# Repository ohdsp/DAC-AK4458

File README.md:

# [Open Hardware DSP Platform](http://www.ohdsp.org)
## DAC-AK4458
### Revision 1.0
### 8 Differential DAC Output Board

---
# README
### Disclaimer
Copyright Paul Janicki 2019

Licensed under the TAPR Open Hardware License (www.tapr.org/OHL)

This documentation is distributed WITHOUT ANY EXPRESS OR IMPLIED WARRANTY, INCLUDING OF MERCHANTABILITY, SATISFACTORY QUALITY AND FITNESS FOR A PARTICULAR PURPOSE.

### What is this repository?

**Quick summary**

This is Open Hardware DSP Platform DAC-AK4458 Revision 1.0. 

This is an 8 differential outputb DAC board based on the AK4458.

This repository contains the KiCad design files, manufacturing Gerber/drill files, PDF/drawing files, and relevant documenation for this board.

### What is the project folder structure?
Most folder names are self explanatory. Starting from the top level: \
*DAC-AK4458*
+ *Bill of Materials*  - This contains the bill of materials in CVS, LibreOffice Calc and XML formats
+ *Drawings* - This contains PDF and SVG Schematic and PCB files
+ *Gerbers* - This contains the PCB Gerbers and drill drawings for manufacture, there is also a zip file ready to send to most manufacturers
+ *JPEGs* - JPEGs of top and bottom views from 3D viewer
+ *KiCad* - This contains the original KiCad schematic and PCB design files
+ *Pick and Place* - This contains pick and place files for top and bottom sides
### How do I get set up?

**Summary of set up**

1. Set your self up a directory on a local disk, something simple will make life easier (eg C:\Electronics on Windows as used here), but anywhere will do just fine.
2. Download the Kicad-Libs from [https://github.com/ohdsp/KiCad-Libs](https://github.com/ohdsp/KiCad-Libs) and place in C:\Electronics\Kicad-Libs (or your chosen folder) 
3. Create a OHDSP subdirectory in C:\Electronics (so C:\Electronics\OHDSP)
3. Download this project to C:\Electronics\OHDSP\DAC-AK4458
4. Fire up Kicad
5. Open the main project file C:\Electronics\OHDSP\DAC-AK4458\KiCad\DAC-AK4458-1.0.pro
7. Do as you wish with the project, just keep it under the TAPR Open Hardware License.
Note: For library issues see below.

Make sure your git setup doesn't exclude files used in the project (like .LIB files) or things may go wrong down the line.

**KiCad Library Configuration**

Note that libraries are setup using relative paths, if you follow the above instructions things should work just fine. Below is the default library setup.

To setup eeschema component libraries:
From KiCad main window go to menu Tools -> Edit Schematic Symbols. In the new Window go to menu Preferences -> Manage Symbol Libraries.

On the new "Symbol Libraries" window select the "Project Specific Libraries" tab. The "Append Library" and "Remove Library" buttons can be used to add/remove enteries.
The standard setup is:

|   | Active | Nickname        | Library Path                                        | Plugin Type | Options | Description |
|---|--------|-----------------|-----------------------------------------------------|-------------|---------|-------------|
| 1 | Ticked | power           | ${KICAD_SYMBOL_DIR}/power.lib                       | Legacy      | (blank) | (blank)     |
| 2 | Ticked | MyKiCadLibs-Lib | ${KIPRJMOD}/../../../KiCad-Libs/MyKiCadLibs-Lib.lib | Legacy      | (blank) | (blank)     |

${KICAD_SYMBOL_DIR}  is set under the Enviromnet Variable Configuration. Close Symbol Libraries dialogue and go "Preferences" -> "Configure Paths..."

${KICAD_SYMBOL_DIR} is set to C:\Program Files\KiCad\share\kicad\library - this is the default for a KiCad install on the C drive

${KIPRJMOD} is automatically set to the location of the project (.pro file), in this example this would be C:\Electronics\OHDSP\uDSP\KiCad

To setup Pcbnew libraries:
From KiCad main window go to menu Tools -> Edit PCB Footprints. In the new Window go to menu Preferences -> Manage Symbol Libraries.

On the new "Symbol Libraries" window select the "Project Specific Libraries" tab. The "Append Library" and "Remove Library" buttons can be used to add/remove enteries.
The standard setup is:

|   | Active | Nickname               | Library Path                                                  | Plugin Type | Options | Description |
|---|--------|------------------------|---------------------------------------------------------------|-------------|---------|-------------|
| 1 | Ticked | MyKiCadLibs-Footprints | ${KIPRJMOD}/../../../KiCad-Libs/MyKiCadLibs-Footprints.pretty | KiCad       | (blank) | (blank)     |

${KIPRJMOD} is automatically set to the location of the project (.pro file), in this example this would be C:\Electronics\OHDSP\uDSP\KiCad

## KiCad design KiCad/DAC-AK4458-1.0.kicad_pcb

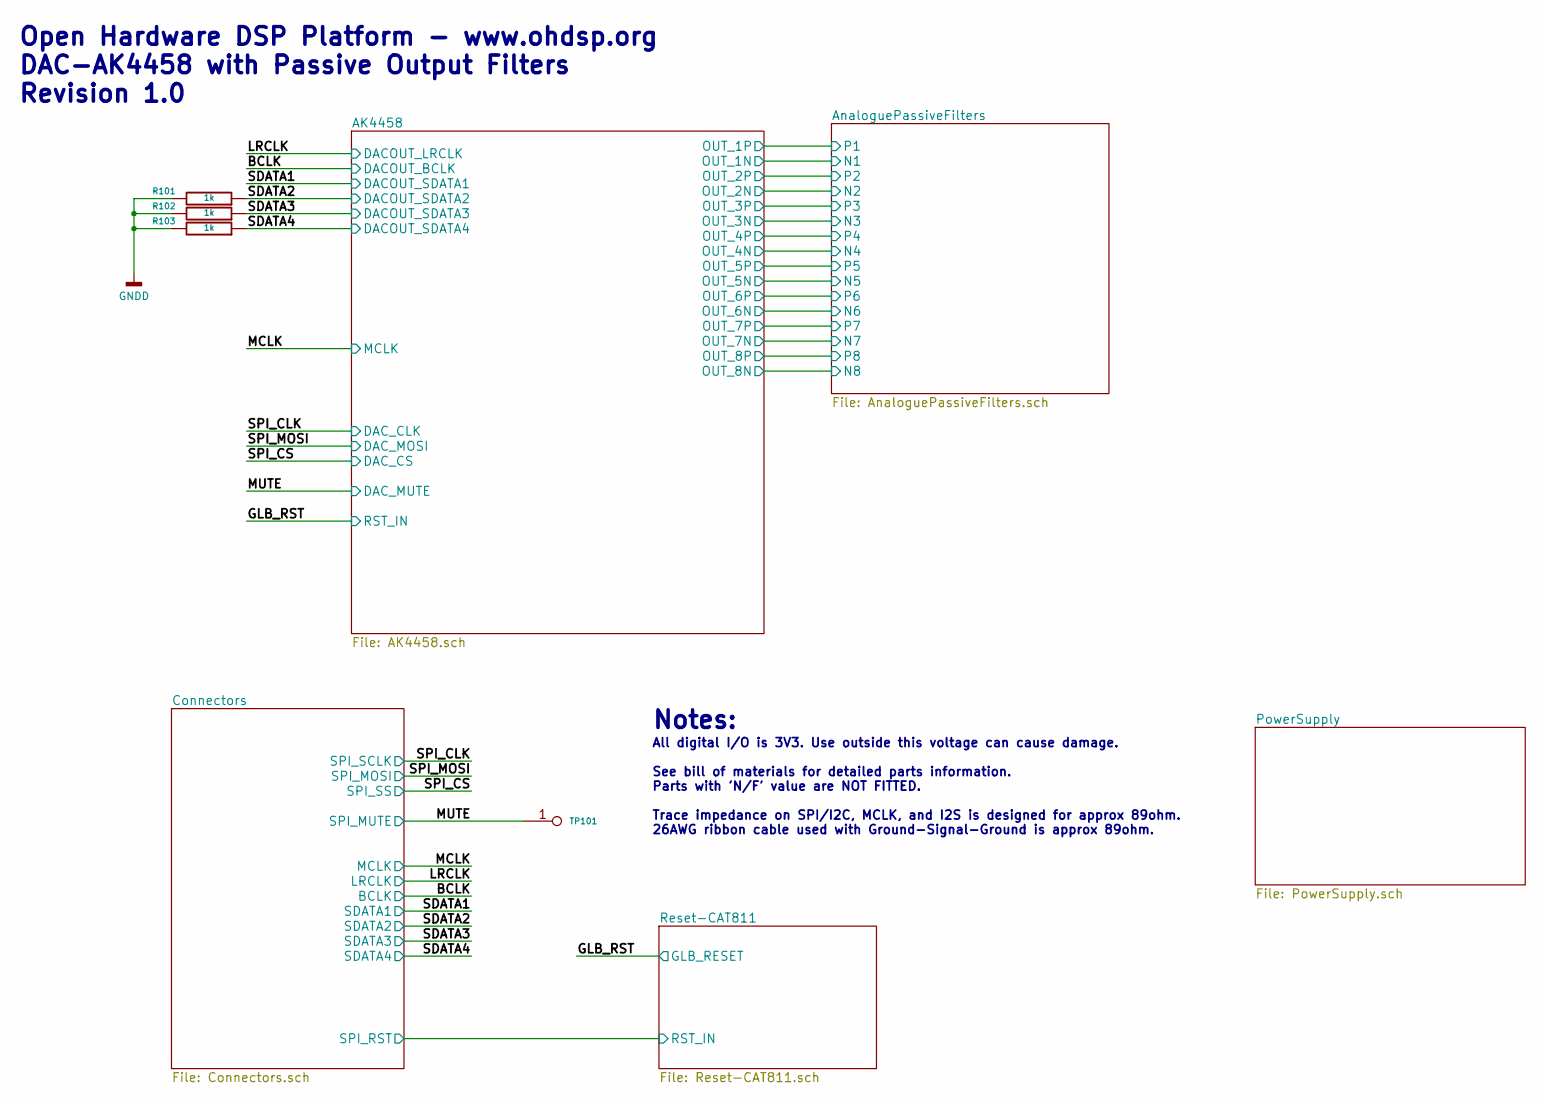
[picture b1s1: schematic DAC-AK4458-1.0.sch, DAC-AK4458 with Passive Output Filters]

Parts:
R101, R102, R103: 1k; SMD-0805; Tolerance 1%
TP101: Test point; TP-1mm

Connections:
/MUTE: TP101.1; also elsewhere on the board
/SDATA2: R101.1; also elsewhere on the board
/SDATA3: R102.1; also elsewhere on the board
/SDATA4: R103.1; also elsewhere on the board
GNDA: R101.2, R102.2, R103.2; also elsewhere on the board

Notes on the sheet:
Open Hardware DSP Platform - www.ohdsp.org DAC-AK4458 with Passive Output Filters Revision 1.0
All digital I/O is 3V3. Use outside this voltage can cause damage. See bill of materials for detailed parts information. Parts with 'N/F' value are NOT FITTED. Trace impedance on SPI/I2C, MCLK, and I2S is designed for approx 89ohm. 26AWG ribbon cable used with Ground-Signal-Ground is approx 89ohm.
Notes:

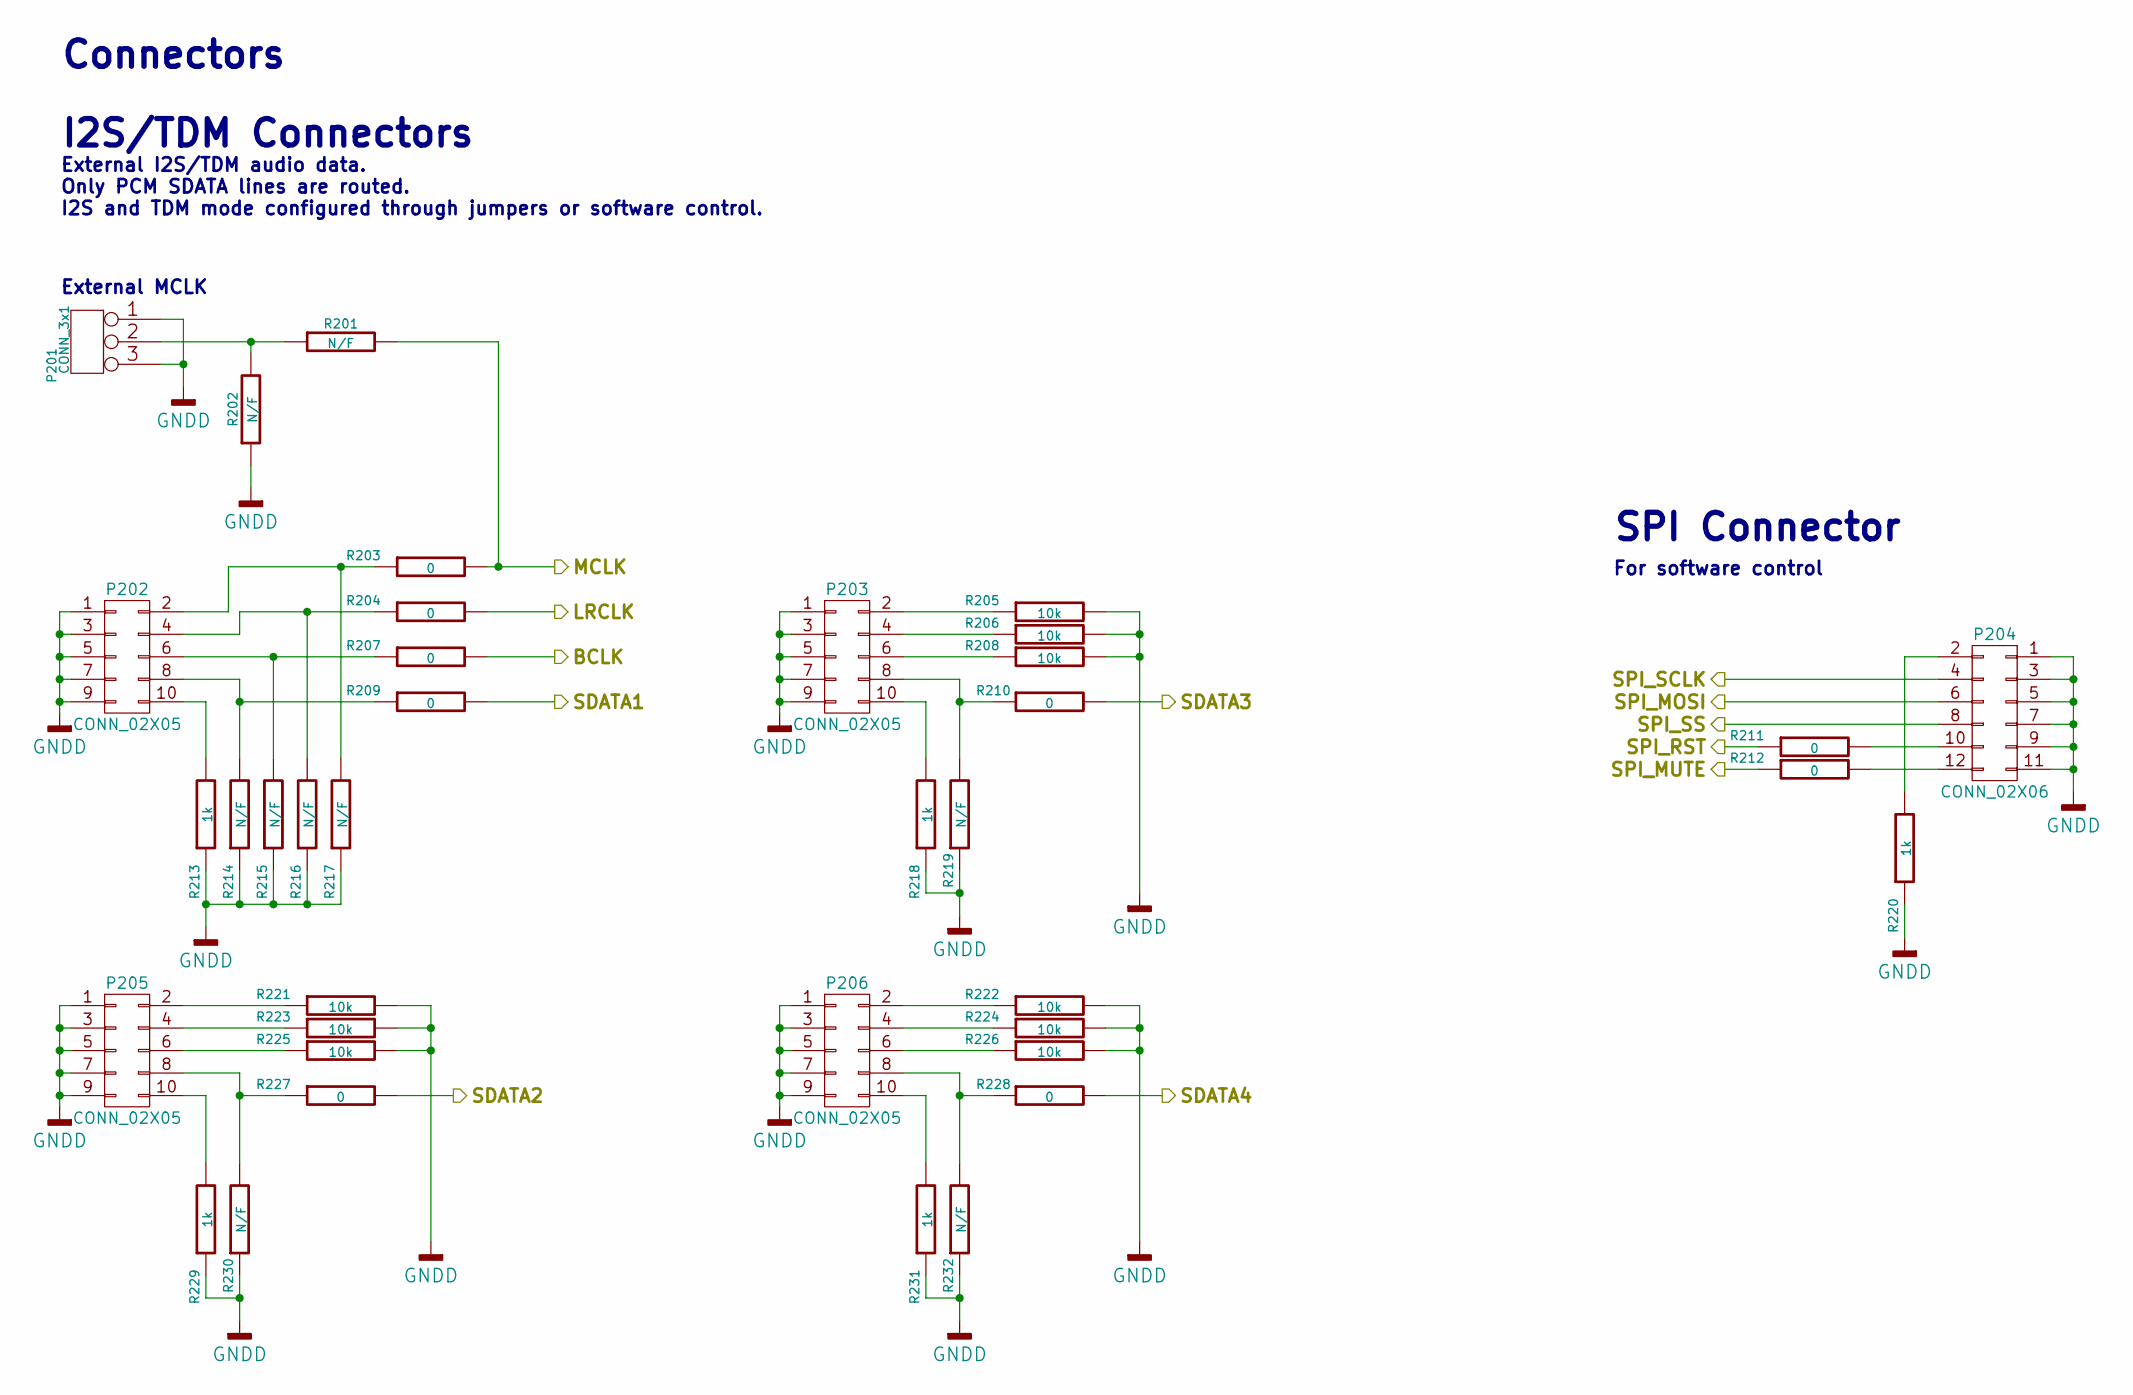
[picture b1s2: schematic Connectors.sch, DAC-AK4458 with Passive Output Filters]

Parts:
P201: CONN_3x1; CONN_SIL_3_1MM
P202, P203, P205, P206: CONN_02X05; CONN_DIL_2X5_BOX_1MM
P204: CONN_02X06; CONN_DIL_2X6_BOX_1MM
R201, R202, R214, R215, R216, R217, R219, R230, R232: N/F; SMD-0805; Tolerance 1%
R203, R204, R207, R209, R210, R211, R212, R227, R228: 0; SMD-0805; Tolerance 1%
R205, R206, R208, R221, R222, R223, R224, R225, R226: 10k; SMD-0805; Tolerance 1%
R213, R218, R220, R229, R231: 1k; SMD-0805; Tolerance 1%

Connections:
/BCLK: R207.2; also elsewhere on the board
/LRCLK: R204.2; also elsewhere on the board
/MCLK: R201.2, R203.2; also elsewhere on the board
/MUTE: R212.1; also elsewhere on the board
/Reset-CAT811/RST_IN: R211.1; also elsewhere on the board
/SDATA1: R209.2; also elsewhere on the board
/SDATA2: R227.2; also elsewhere on the board
/SDATA3: R210.2; also elsewhere on the board
/SDATA4: R228.2; also elsewhere on the board
/SPI_CLK: P204.4; also elsewhere on the board
/SPI_CS: P204.8; also elsewhere on the board
/SPI_MOSI: P204.6; also elsewhere on the board
GNDA: P201.1, P201.3, P202.1, P202.3, P202.5, P202.7, P202.9, P203.1, P203.3, P203.5, P203.7, P203.9, P204.1, P204.3, P204.5, P204.7, P204.9, P204.11, P205.1, P205.3, P205.5, P205.7, P205.9, P206.1, P206.3, P206.5, P206.7, P206.9, R202.1, R205.2, R206.2, R208.2, R213.1, R214.1, R215.1, R216.1, R217.1, R218.1, R219.1, R220.1, R221.2, R222.2, R223.2, R224.2, R225.2, R226.2, R229.1, R230.1, R231.1, R232.1; also elsewhere on the board
unnamed: P201.2, R201.1, R202.2
unnamed: P202.2, R203.1, R217.2
unnamed: P202.4, R204.1, R216.2
unnamed: P202.6, R207.1, R215.2
unnamed: P202.8, R209.1, R214.2
unnamed: P202.10, R213.2
unnamed: P203.2, R205.1
unnamed: P203.4, R206.1
unnamed: P203.6, R208.1
unnamed: P203.8, R210.1, R219.2
unnamed: P203.10, R218.2
unnamed: P204.2, R220.2
unnamed: P204.10, R211.2
unnamed: P204.12, R212.2
unnamed: P205.2, R221.1
unnamed: P205.4, R223.1
unnamed: P205.6, R225.1
unnamed: P205.8, R227.1, R230.2
unnamed: P205.10, R229.2
unnamed: P206.2, R222.1
unnamed: P206.4, R224.1
unnamed: P206.6, R226.1
unnamed: P206.8, R228.1, R232.2
unnamed: P206.10, R231.2

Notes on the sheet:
SPI Connector
I2S/TDM Connectors
External MCLK
External I2S/TDM audio data. Only PCM SDATA lines are routed. I2S and TDM mode configured through jumpers or software control.
For software control
Connectors

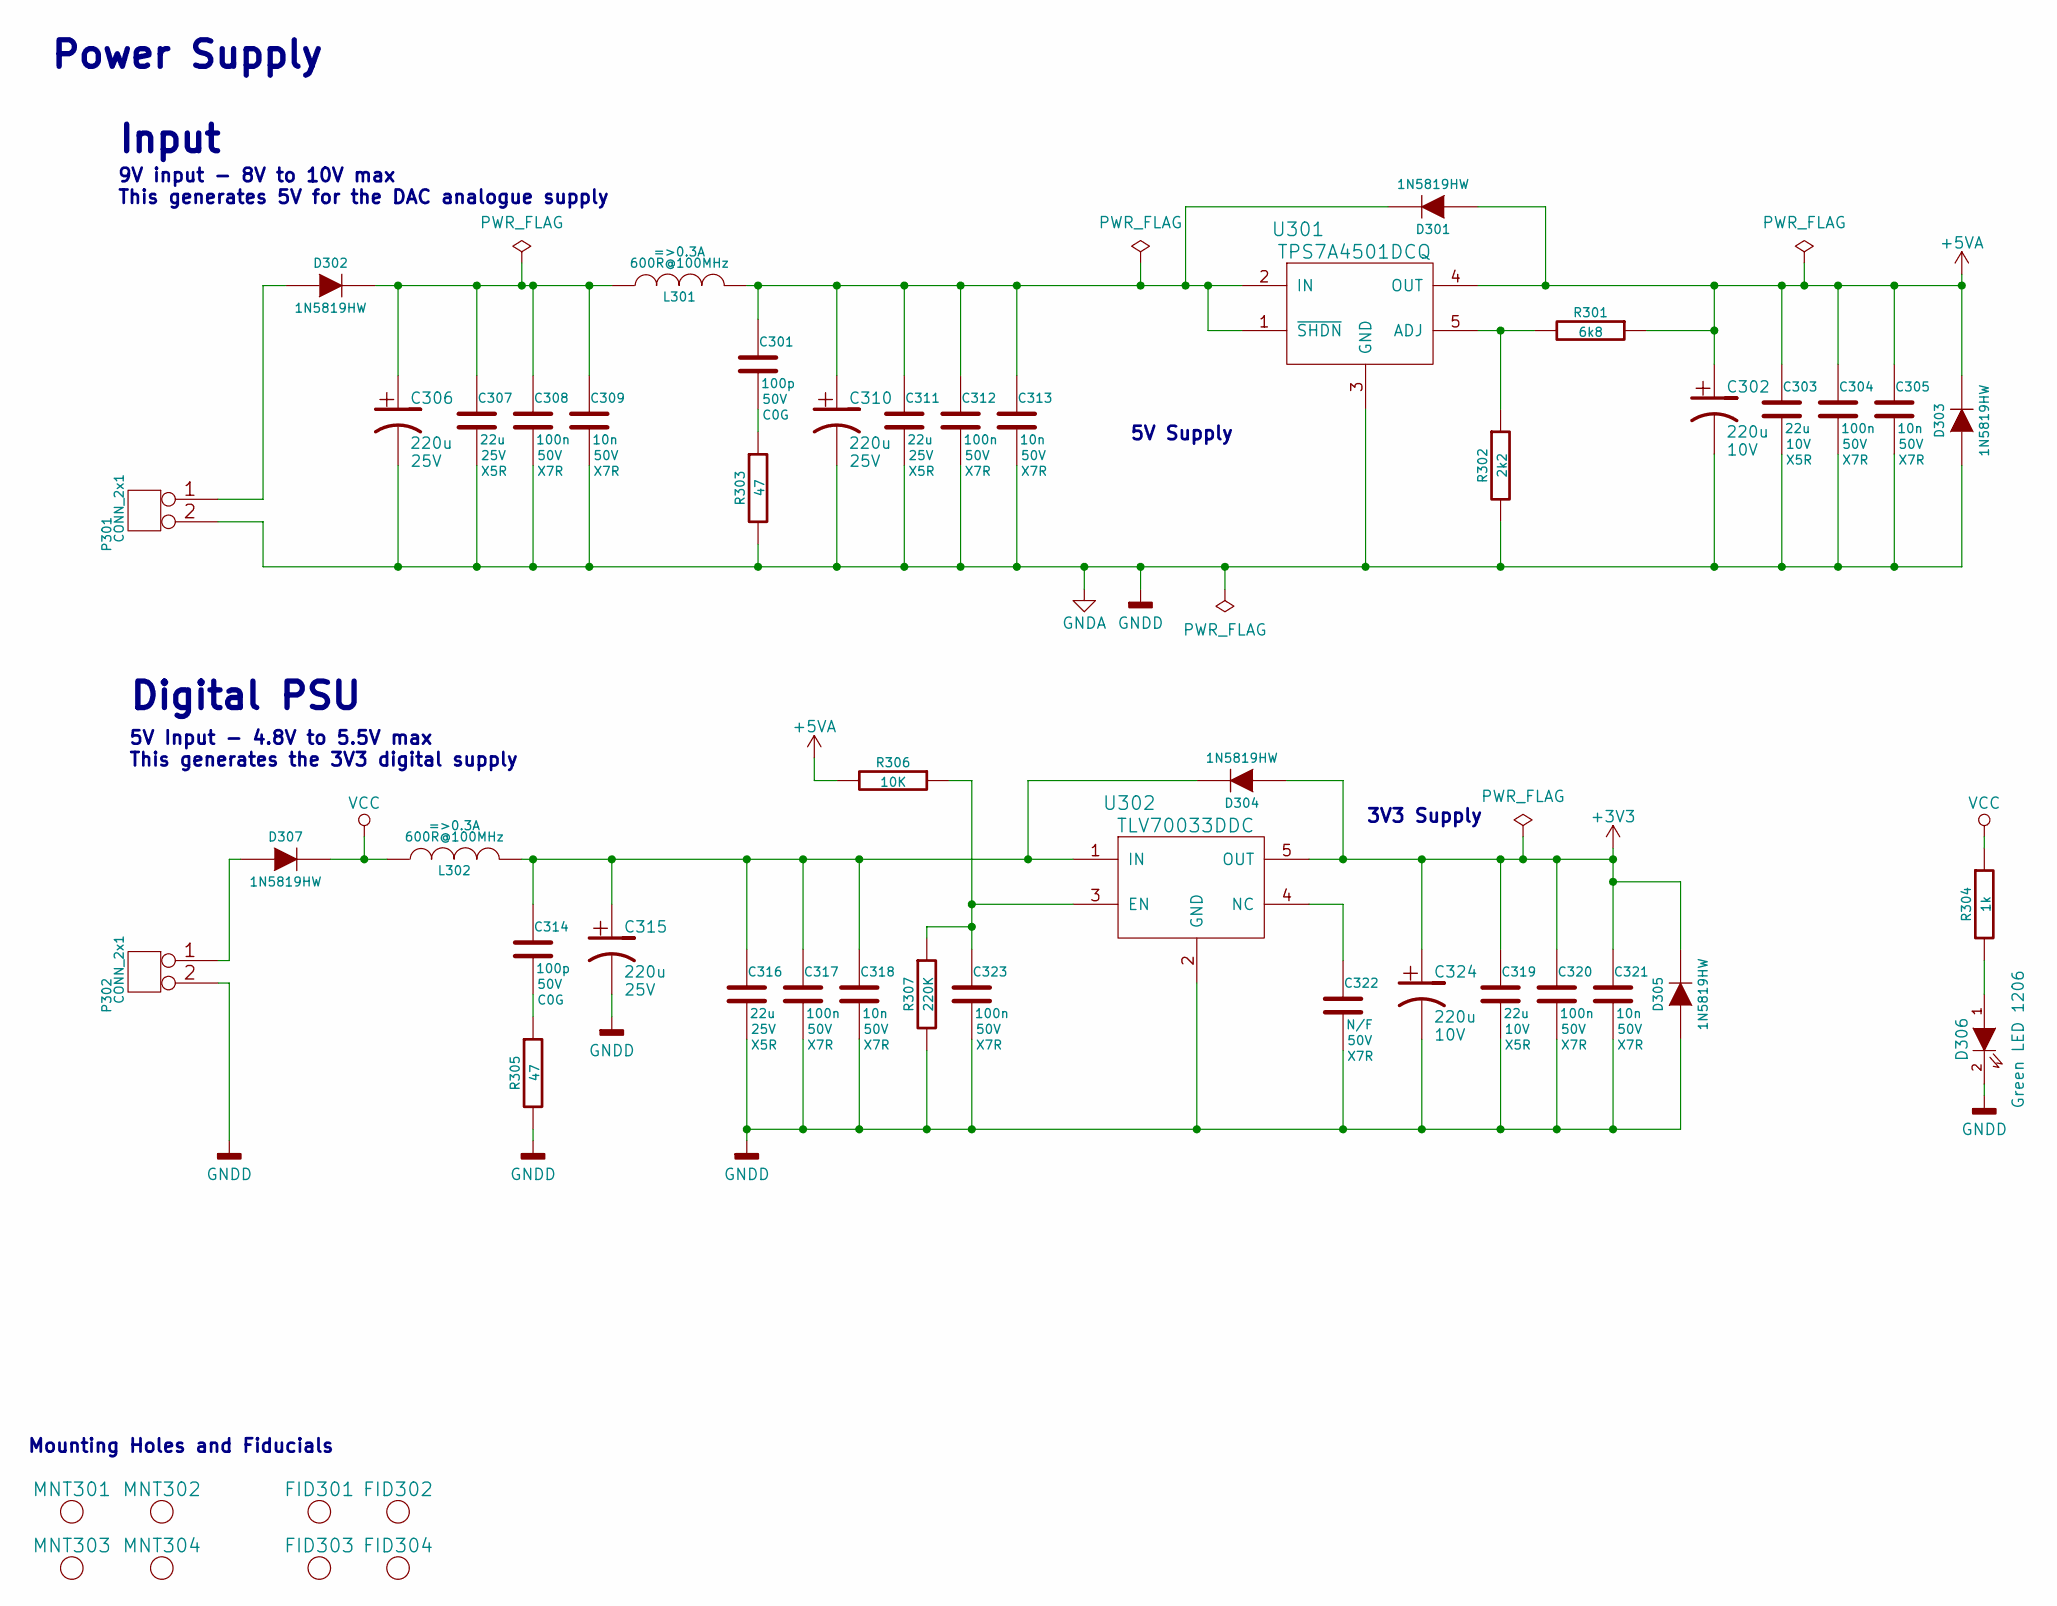
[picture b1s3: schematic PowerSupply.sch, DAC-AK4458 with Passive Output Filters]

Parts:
C301, C314: 100p; SMD-0805; Voltage 50V; Tolerance 5%
C302, C324: 220u; CAP-TH-D6.3mmP2.5mm; Voltage 10V
C303, C319: 22u; SMD-0805; Voltage 10V; Tolerance 20%
C304, C308, C312, C317, C320, C323: 100n; SMD-0805; Voltage 50V; Tolerance 10%
C305, C309, C313, C318, C321: 10n; SMD-0805; Voltage 50V; Tolerance 10%
C306, C310, C315: 220u; CAP-TH-D8mmP3.5mm; Voltage 25V
C307, C311, C316: 22u; SMD-0805; Voltage 25V; Tolerance 20%
C322: N/F; SMD-0805; Voltage 50V; Tolerance 10%
D301, D302, D303, D304, D305, D307: 1N5819HW; DIODE-SOD-123
D306: Green LED 1206; SMD-1206
FID301, FID302, FID303, FID304: MNT_HOLE; FID-1MM-3MM
L301, L302: 600R@100MHz; SMD-0805
MNT301, MNT302, MNT303, MNT304: MNT_HOLE; MNT_HOLE_3.2mm
P301, P302: CONN_2x1; CONN-2WAY-2.54mm-3.81mm-SPACING
R301: 6k8; SMD-0805; Tolerance 1%
R302: 2k2; SMD-0805; Tolerance 1%
R303, R305: 47; SMD-0805; Tolerance 1%
R304: 1k; SMD-0805; Tolerance 1%
R306: 10K; SMD-0805; Tolerance 1%
R307: 220K; SMD-0805; Tolerance 1%
U301: TPS7A4501DCQ; IC-SOT223-6
U302: TLV70033DDC; IC-SOT23-5

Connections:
+3V3: C319.1, C320.1, C321.1, C324.1, D304.1 (A), D305.2 (K), U302.5 (OUT); also elsewhere on the board
+5VA: C302.1, C303.1, C304.1, C305.1, D301.1 (A), D303.2 (K), R301.1, R306.2, U301.4 (OUT); also elsewhere on the board
GNDA: C302.2, C303.2, C304.2, C305.2, C306.2, C307.2, C308.2, C309.2, C310.2, C311.2, C312.2, C313.2, C315.2, C316.2, C317.2, C318.2, C319.2, C320.2, C321.2, C322.2, C323.2, C324.2, D303.1 (A), D305.1 (A), D306.2 (K), P301.2, P302.2, R302.2, R303.2, R305.2, R307.2, U301.3 (GND), U302.2 (GND); also elsewhere on the board
unnamed: C301.1, C310.1, C311.1, C312.1, C313.1, D301.2 (K), L301.2, U301.1 (~SHDN), U301.2 (IN)
unnamed: C301.2, R303.1
unnamed: C306.1, C307.1, C308.1, C309.1, D302.2 (K), L301.1
unnamed: C314.1, C315.1, C316.1, C317.1, C318.1, D304.2 (K), L302.2, U302.1 (IN)
unnamed: C314.2, R305.1
unnamed: C322.1, U302.4 (NC)
unnamed: C323.1, R306.1, R307.1, U302.3 (EN)
unnamed: D302.1 (A), P301.1
unnamed: D306.1 (A), R304.2
unnamed: D307.1 (A), P302.1
unnamed: R301.2, R302.1, U301.5 (ADJ)
VCC: D307.2 (K), L302.1, R304.1

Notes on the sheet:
Mounting Holes and Fiducials
Input
Digital PSU
9V input - 8V to 10V max This generates 5V for the DAC analogue supply
5V Input - 4.8V to 5.5V max This generates the 3V3 digital supply
5V Supply
3V3 Supply
Power Supply

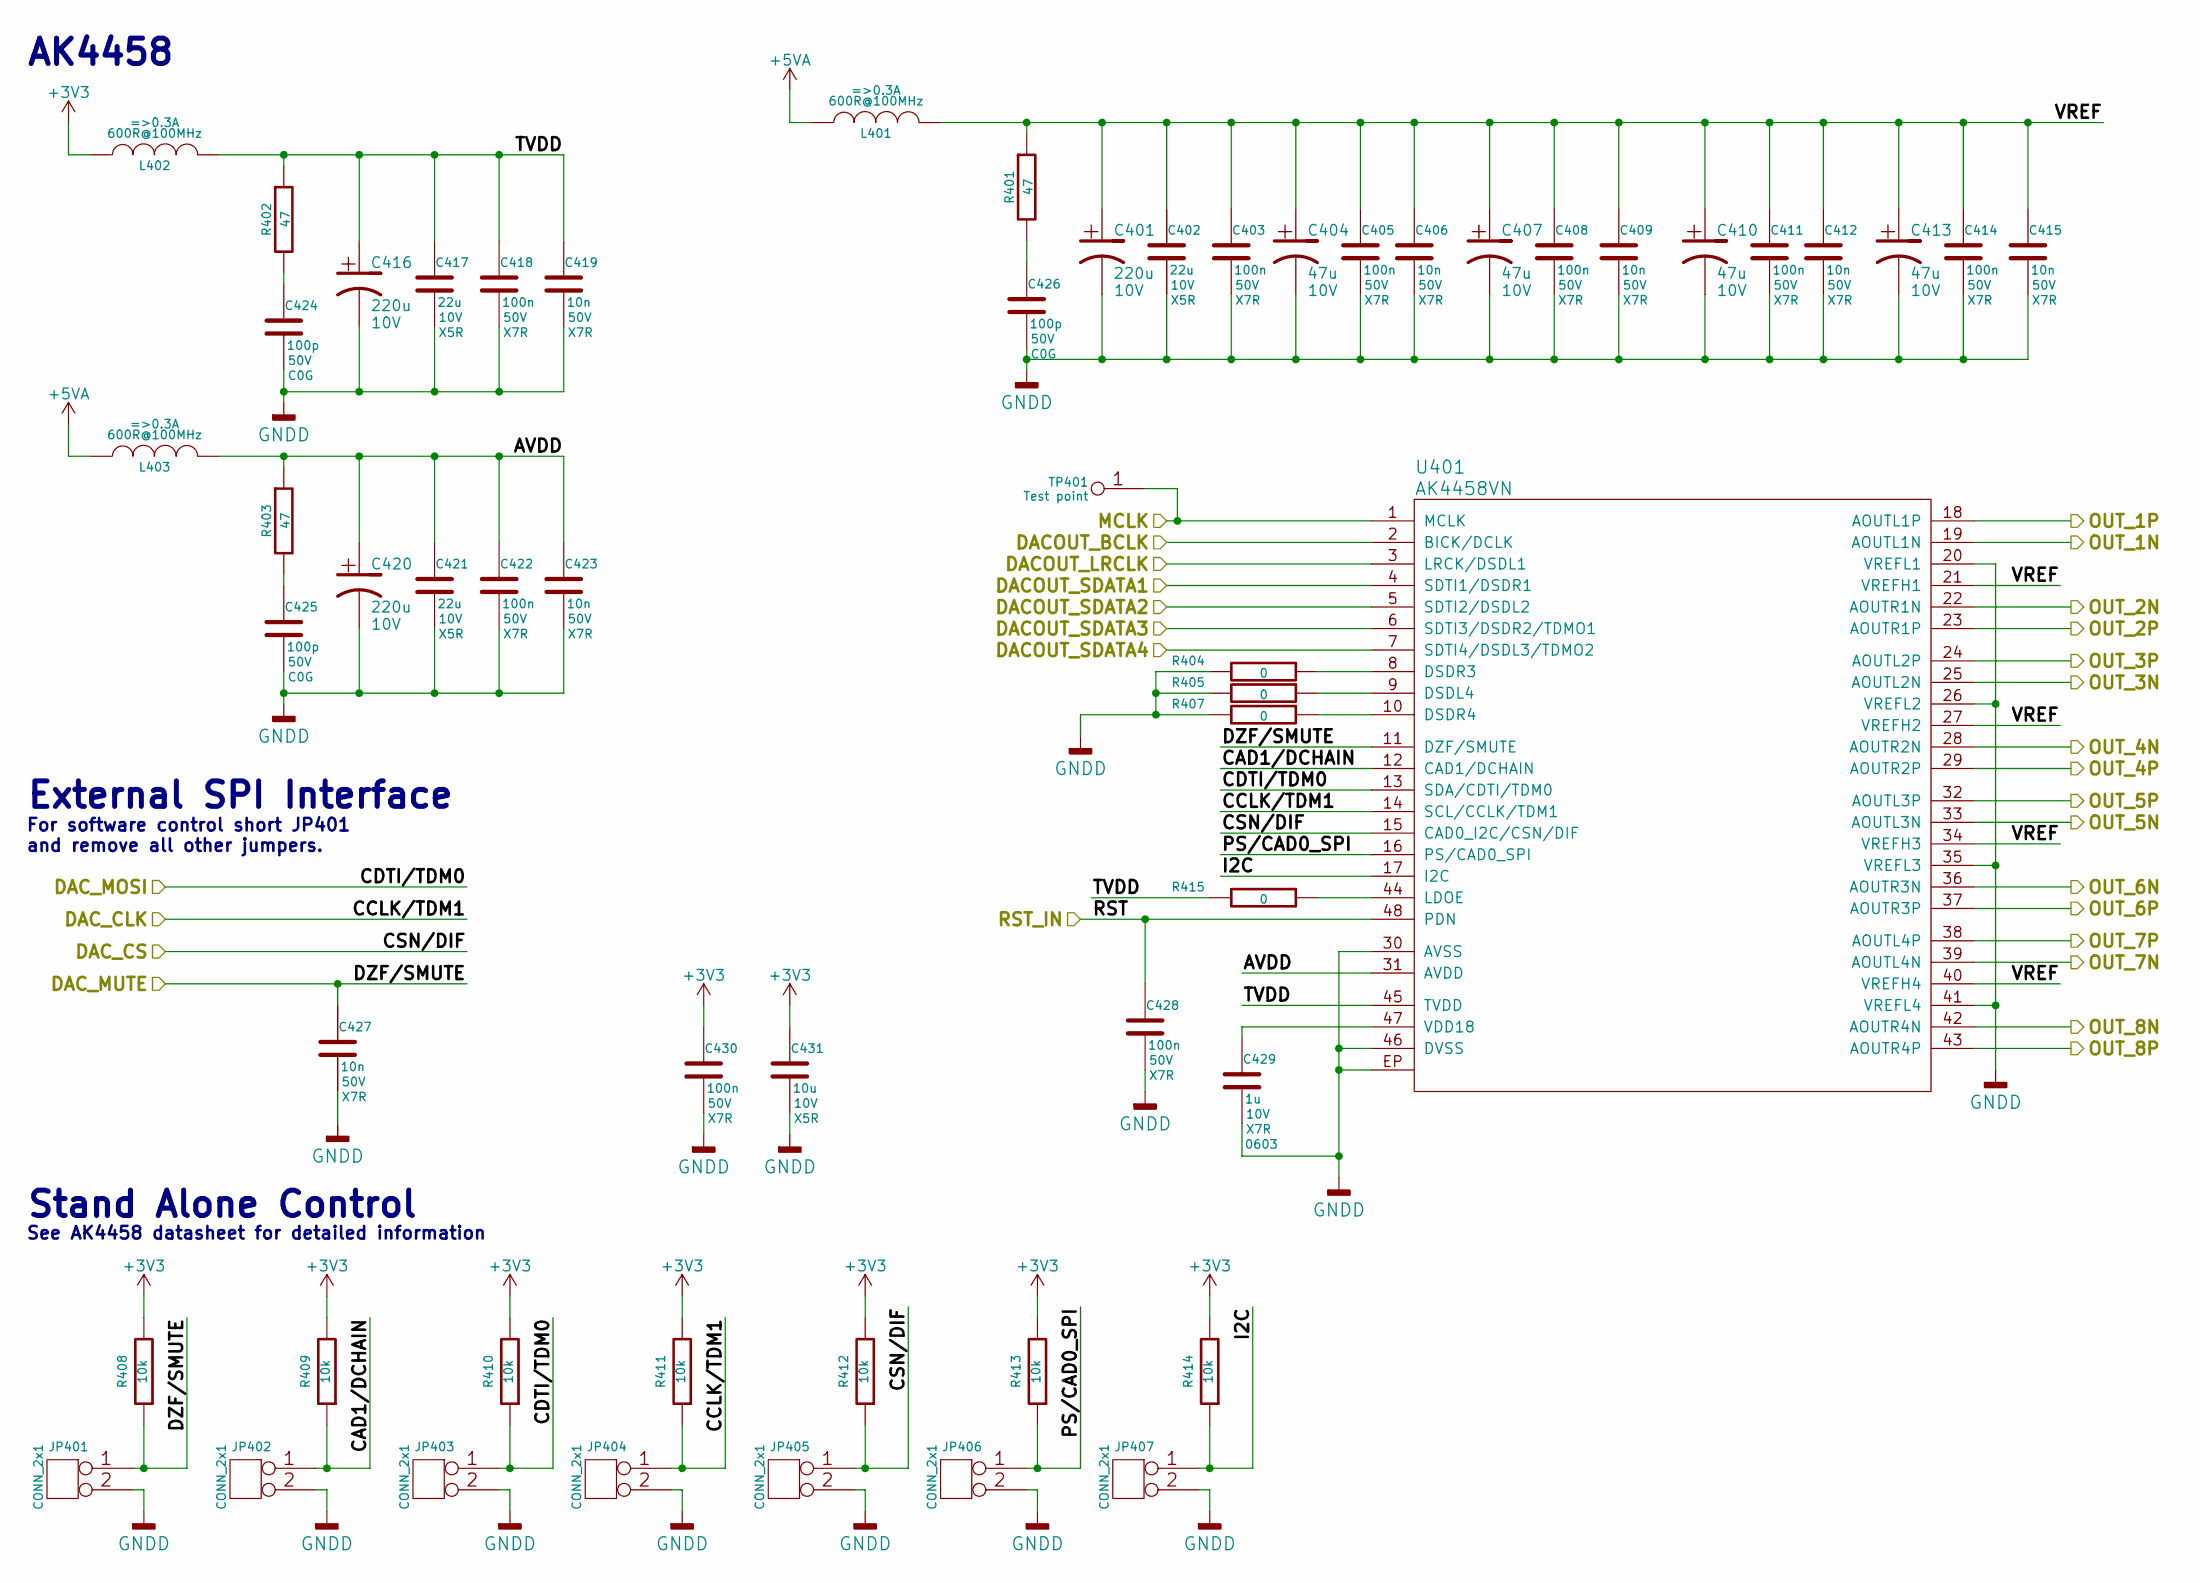
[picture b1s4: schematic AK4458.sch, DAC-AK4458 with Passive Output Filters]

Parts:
C401, C416, C420: 220u; CAP-TH-D6.3mmP2.5mm; Voltage 10V
C402, C417, C421: 22u; SMD-0805; Voltage 10V; Tolerance 20%
C403, C405, C408, C411, C414, C418, C422, C428, C430: 100n; SMD-0805; Voltage 50V; Tolerance 10%
C404, C407, C410, C413: 47u; CAP-TH-D6.3mmP2.5mm; Voltage 10V
C406, C409, C412, C415, C419, C423, C427: 10n; SMD-0805; Voltage 50V; Tolerance 10%
C424, C425, C426: 100p; SMD-0805; Voltage 50V; Tolerance 5%
C429: 1u; SMD-0603; Voltage 10V; Tolerance 10%
C431: 10u; SMD-0805; Voltage 10V; Tolerance 20%
JP401, JP402, JP403, JP404, JP405, JP406, JP407: CONN_2x1; CONN_SIL_2_1MM
L401, L402, L403: 600R@100MHz; SMD-0805
R401, R402, R403: 47; SMD-0805; Tolerance 1%
R404, R405, R407, R415: 0; SMD-0805; Tolerance 1%
R408, R409, R410, R411, R412, R413, R414: 10k; SMD-0805; Tolerance 1%
TP401: Test point; TP-1mm
U401: AK4458VN; IC_QFN_48_5.1mmpad_HF_HS

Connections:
+3V3: C430.1, C431.1, L402.1, R408.2, R409.2, R410.2, R411.2, R412.2, R413.2, R414.2; also elsewhere on the board
+5VA: L401.1, L403.1; also elsewhere on the board
/AK4458/AVDD: C420.1, C421.1, C422.1, C423.1, L403.2, R403.1, U401.31 (AVDD)
/AK4458/CAD1/DCHAIN: JP402.1, R409.1, U401.12 (CAD1/DCHAIN)
/AK4458/I2C: JP407.1, R414.1, U401.17 (I2C)
/AK4458/OUT_1P: U401.18 (AOUTL1P); also elsewhere on the board
/AK4458/OUT_2P: U401.23 (AOUTR1P); also elsewhere on the board
/AK4458/OUT_3P: U401.24 (AOUTL2P); also elsewhere on the board
/AK4458/OUT_4P: U401.29 (AOUTR2P); also elsewhere on the board
/AK4458/OUT_5P: U401.32 (AOUTL3P); also elsewhere on the board
/AK4458/OUT_6P: U401.37 (AOUTR3P); also elsewhere on the board
/AK4458/OUT_7P: U401.38 (AOUTL4P); also elsewhere on the board
/AK4458/OUT_8P: U401.43 (AOUTR4P); also elsewhere on the board
/AK4458/PS/CAD0_SPI: JP406.1, R413.1, U401.16 (PS/CAD0_SPI)
/AK4458/TVDD: C416.1, C417.1, C418.1, C419.1, L402.2, R402.1, R415.2, U401.45 (TVDD)
/AK4458/VREF: C401.1, C402.1, C403.1, C404.1, C405.1, C406.1, C407.1, C408.1, C409.1, C410.1, C411.1, C412.1, C413.1, C414.1, C415.1, L401.2, R401.1, U401.21 (VREFH1), U401.27 (VREFH2), U401.34 (VREFH3), U401.40 (VREFH4)
/AnaloguePassiveFilters/N1: U401.19 (AOUTL1N); also elsewhere on the board
/AnaloguePassiveFilters/N2: U401.22 (AOUTR1N); also elsewhere on the board
/AnaloguePassiveFilters/N3: U401.25 (AOUTL2N); also elsewhere on the board
/AnaloguePassiveFilters/N4: U401.28 (AOUTR2N); also elsewhere on the board
/AnaloguePassiveFilters/N5: U401.33 (AOUTL3N); also elsewhere on the board
/AnaloguePassiveFilters/N6: U401.36 (AOUTR3N); also elsewhere on the board
/AnaloguePassiveFilters/N7: U401.39 (AOUTL4N); also elsewhere on the board
/AnaloguePassiveFilters/N8: U401.42 (AOUTR4N); also elsewhere on the board
/BCLK: U401.2 (BICK/DCLK); also elsewhere on the board
/GLB_RST: C428.1, U401.48 (PDN); also elsewhere on the board
/LRCLK: U401.3 (LRCK/DSDL1); also elsewhere on the board
/MCLK: TP401.1, U401.1 (MCLK); also elsewhere on the board
/MUTE: C427.1, JP401.1, R408.1, U401.11 (DZF/SMUTE); also elsewhere on the board
/SDATA1: U401.4 (SDTI1/DSDR1); also elsewhere on the board
/SDATA2: U401.5 (SDTI2/DSDL2); also elsewhere on the board
/SDATA3: U401.6 (SDTI3/DSDR2/TDMO1); also elsewhere on the board
/SDATA4: U401.7 (SDTI4/DSDL3/TDMO2); also elsewhere on the board
/SPI_CLK: JP404.1, R411.1, U401.14 (SCL/CCLK/TDM1); also elsewhere on the board
/SPI_CS: JP405.1, R412.1, U401.15 (CAD0_I2C/CSN/DIF); also elsewhere on the board
/SPI_MOSI: JP403.1, R410.1, U401.13 (SDA/CDTI/TDM0); also elsewhere on the board
GNDA: C401.2, C402.2, C403.2, C404.2, C405.2, C406.2, C407.2, C408.2, C409.2, C410.2, C411.2, C412.2, C413.2, C414.2, C415.2, C416.2, C417.2, C418.2, C419.2, C420.2, C421.2, C422.2, C423.2, C424.2, C425.2, C426.2, C427.2, C428.2, C429.2, C430.2, C431.2, JP401.2, JP402.2, JP403.2, JP404.2, JP405.2, JP406.2, JP407.2, R404.2, R405.2, R407.2, U401.20 (VREFL1), U401.26 (VREFL2), U401.30 (AVSS), U401.35 (VREFL3), U401.41 (VREFL4), U401.46 (DVSS), U401.EP; also elsewhere on the board
unnamed: C424.1, R402.2
unnamed: C425.1, R403.2
unnamed: C426.1, R401.2
unnamed: C429.1, U401.47 (VDD18)
unnamed: R404.1, U401.8 (DSDR3)
unnamed: R405.1, U401.9 (DSDL4)
unnamed: R407.1, U401.10 (DSDR4)
unnamed: R415.1, U401.44 (LDOE)

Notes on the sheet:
External SPI Interface
Stand Alone Control
For software control short JP401 and remove all other jumpers.
AK4458
See AK4458 datasheet for detailed information

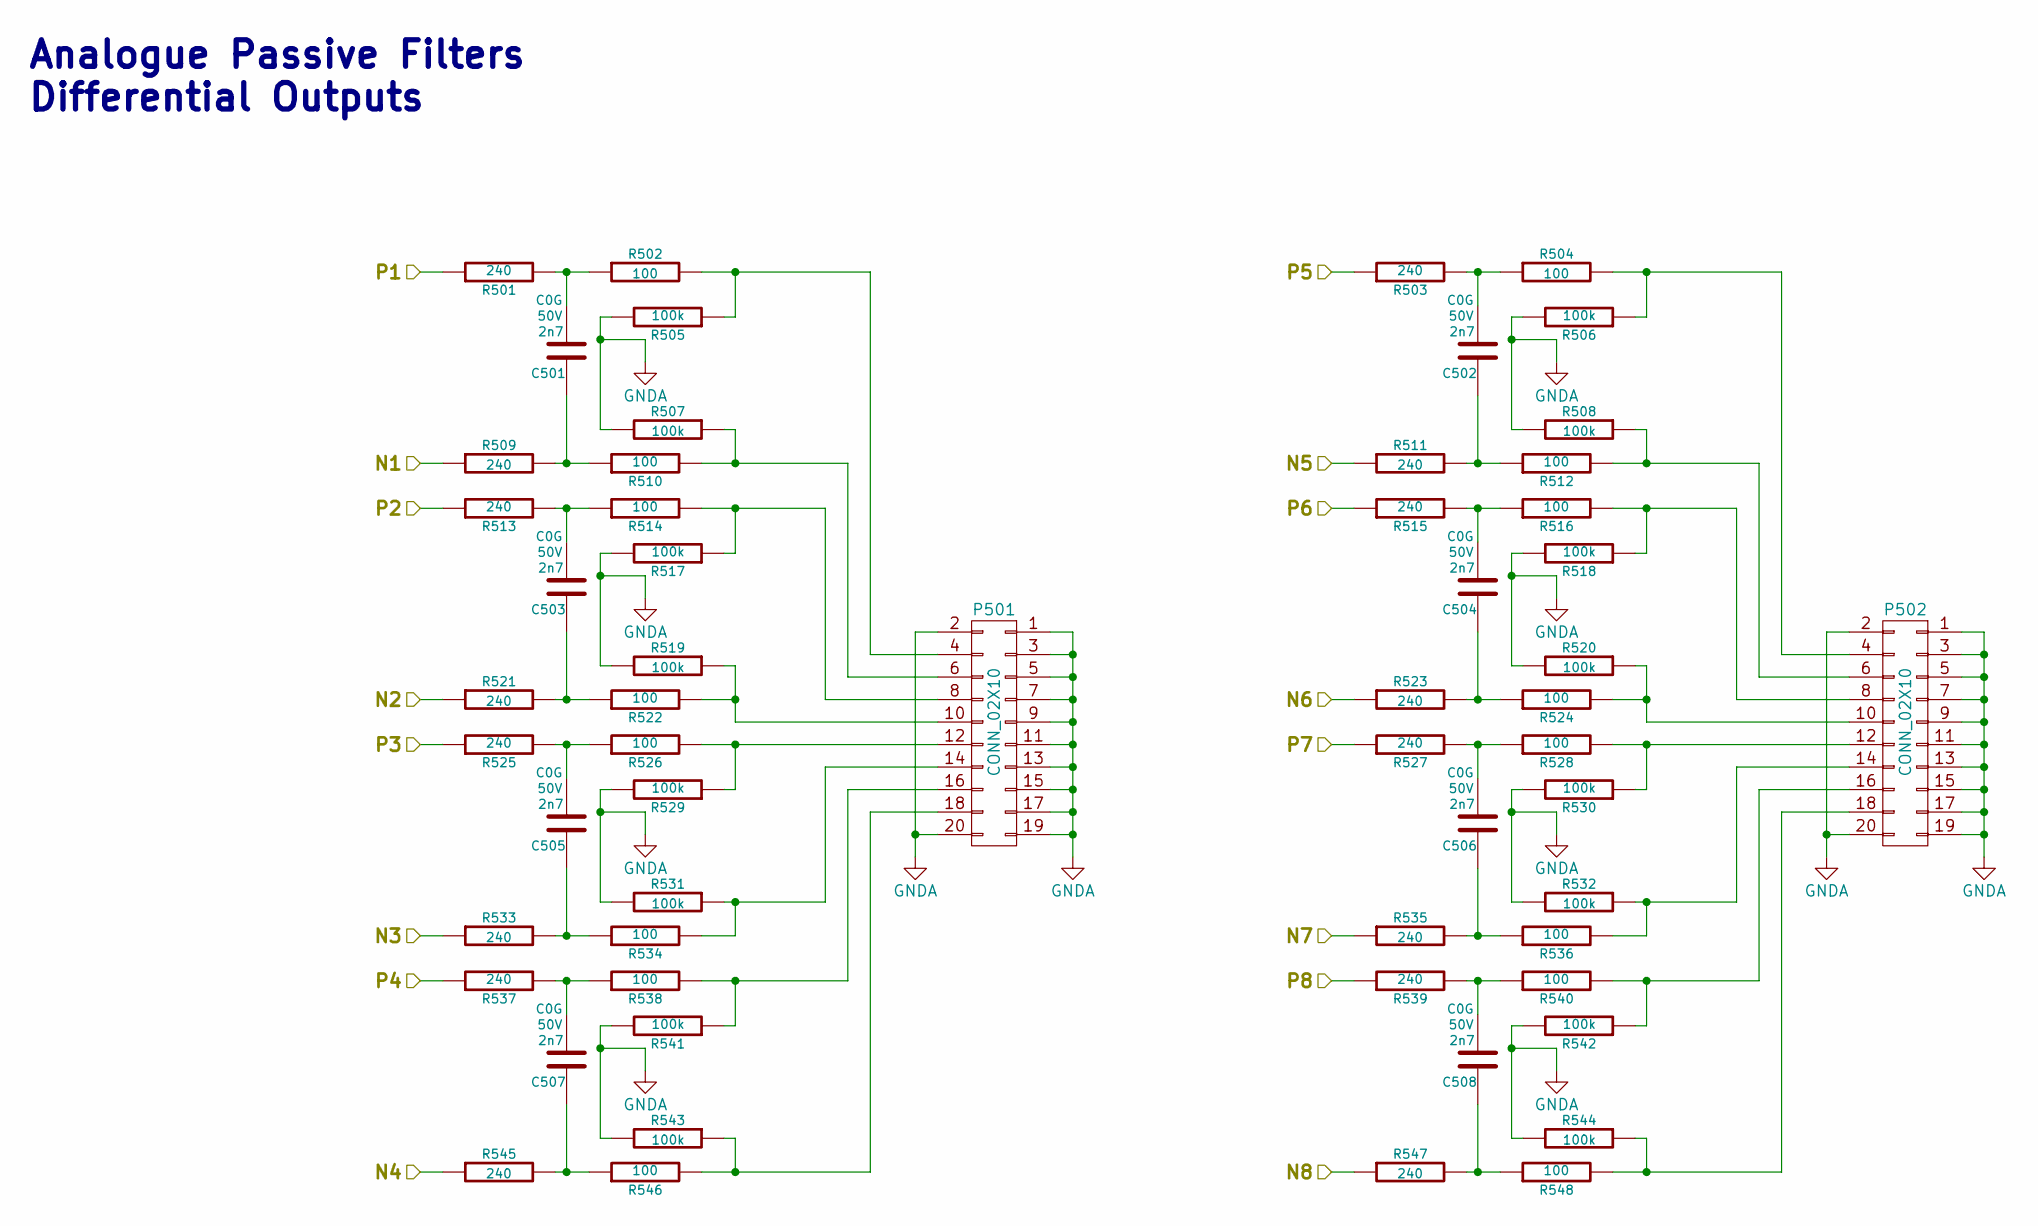
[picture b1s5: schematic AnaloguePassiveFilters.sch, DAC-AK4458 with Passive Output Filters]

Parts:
C501, C502, C503, C504, C505, C506, C507, C508: 2n7; SMD-0805; Voltage 50V; Tolerance 5%
P501, P502: CONN_02X10; CONN_DIL_2X10_BOX_1MM
R501, R503, R509, R511, R513, R515, R521, R523, R525, R527, R533, R535, R537, R539, R545, R547: 240; SMD-1206; Tolerance 1%
R502, R504, R510, R512, R514, R516, R522, R524, R526, R528, R534, R536, R538, R540, R546, R548: 100; SMD-1206; Tolerance 1%
R505, R506, R507, R508, R517, R518, R519, R520, R529, R530, R531, R532, R541, R542, R543, R544: 100k; SMD-1206; Tolerance 1%

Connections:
/AK4458/OUT_1P: R501.1; also elsewhere on the board
/AK4458/OUT_2P: R513.1; also elsewhere on the board
/AK4458/OUT_3P: R525.1; also elsewhere on the board
/AK4458/OUT_4P: R537.1; also elsewhere on the board
/AK4458/OUT_5P: R503.1; also elsewhere on the board
/AK4458/OUT_6P: R515.1; also elsewhere on the board
/AK4458/OUT_7P: R527.1; also elsewhere on the board
/AK4458/OUT_8P: R539.1; also elsewhere on the board
/AnaloguePassiveFilters/N1: R509.1; also elsewhere on the board
/AnaloguePassiveFilters/N2: R521.1; also elsewhere on the board
/AnaloguePassiveFilters/N3: R533.1; also elsewhere on the board
/AnaloguePassiveFilters/N4: R545.1; also elsewhere on the board
/AnaloguePassiveFilters/N5: R511.1; also elsewhere on the board
/AnaloguePassiveFilters/N6: R523.1; also elsewhere on the board
/AnaloguePassiveFilters/N7: R535.1; also elsewhere on the board
/AnaloguePassiveFilters/N8: R547.1; also elsewhere on the board
GNDA: P501.1, P501.2, P501.3, P501.5, P501.7, P501.9, P501.11, P501.13, P501.15, P501.17, P501.19, P501.20, P502.1, P502.2, P502.3, P502.5, P502.7, P502.9, P502.11, P502.13, P502.15, P502.17, P502.19, P502.20, R505.2, R506.2, R507.2, R508.2, R517.2, R518.2, R519.2, R520.2, R529.2, R530.2, R531.2, R532.2, R541.2, R542.2, R543.2, R544.2; also elsewhere on the board
unnamed: C501.1, R509.2, R510.1
unnamed: C501.2, R501.2, R502.1
unnamed: C502.1, R511.2, R512.1
unnamed: C502.2, R503.2, R504.1
unnamed: C503.1, R521.2, R522.1
unnamed: C503.2, R513.2, R514.1
unnamed: C504.1, R523.2, R524.1
unnamed: C504.2, R515.2, R516.1
unnamed: C505.1, R533.2, R534.1
unnamed: C505.2, R525.2, R526.1
unnamed: C506.1, R535.2, R536.1
unnamed: C506.2, R527.2, R528.1
unnamed: C507.1, R545.2, R546.1
unnamed: C507.2, R537.2, R538.1
unnamed: C508.1, R547.2, R548.1
unnamed: C508.2, R539.2, R540.1
unnamed: P501.4, R502.2, R505.1
unnamed: P501.6, R507.1, R510.2
unnamed: P501.8, R514.2, R517.1
unnamed: P501.10, R519.1, R522.2
unnamed: P501.12, R526.2, R529.1
unnamed: P501.14, R531.1, R534.2
unnamed: P501.16, R538.2, R541.1
unnamed: P501.18, R543.1, R546.2
unnamed: P502.4, R504.2, R506.1
unnamed: P502.6, R508.1, R512.2
unnamed: P502.8, R516.2, R518.1
unnamed: P502.10, R520.1, R524.2
unnamed: P502.12, R528.2, R530.1
unnamed: P502.14, R532.1, R536.2
unnamed: P502.16, R540.2, R542.1
unnamed: P502.18, R544.1, R548.2

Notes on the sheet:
Analogue Passive Filters Differential Outputs

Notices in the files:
KiCad/DAC-AK4458-1.0.kicad_pcb:
Licensed under TAPR Open
Copyright ©
